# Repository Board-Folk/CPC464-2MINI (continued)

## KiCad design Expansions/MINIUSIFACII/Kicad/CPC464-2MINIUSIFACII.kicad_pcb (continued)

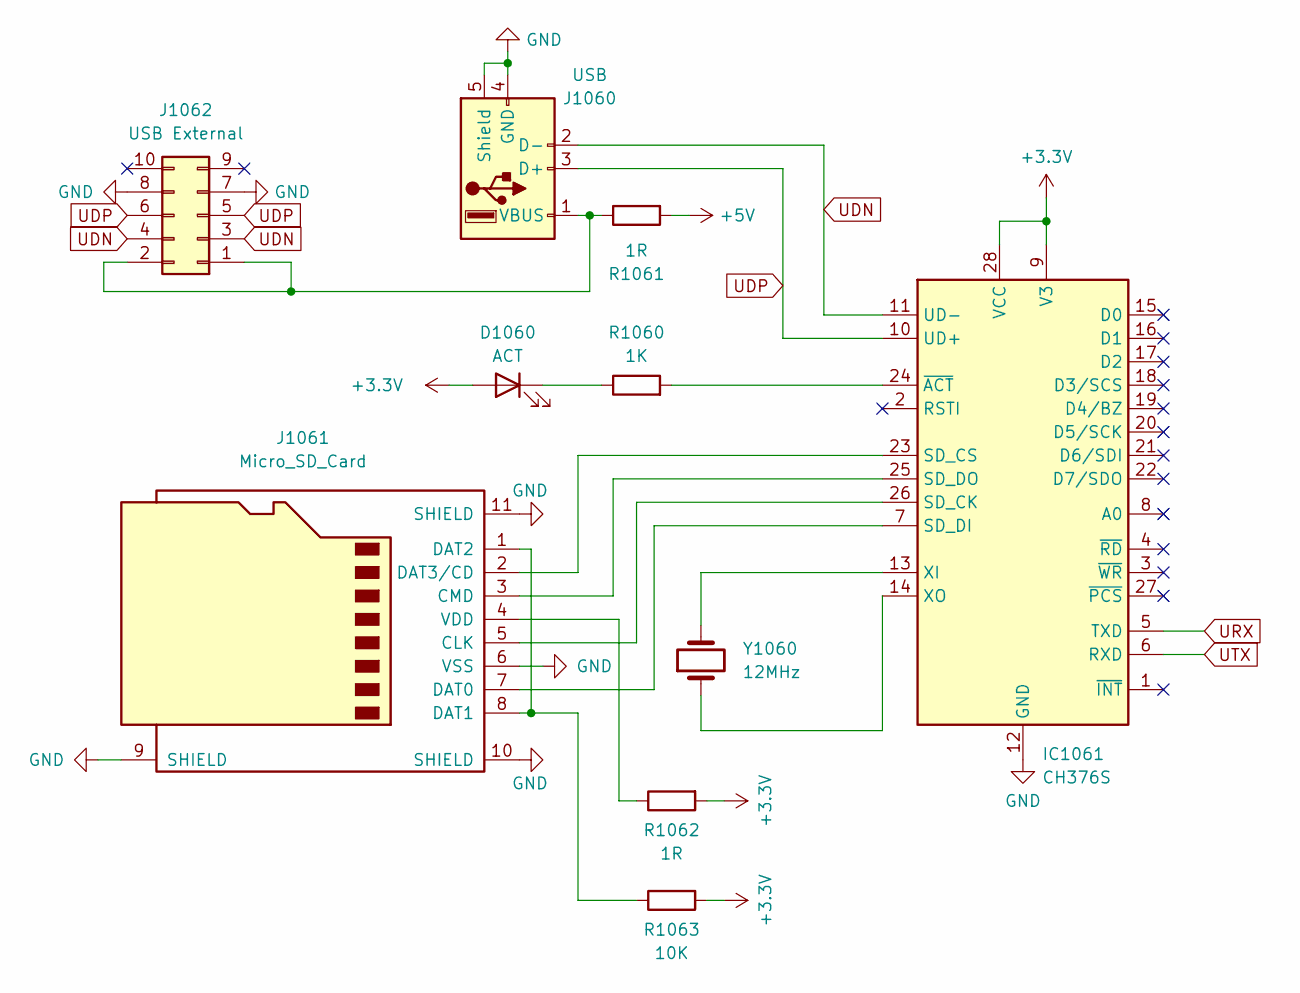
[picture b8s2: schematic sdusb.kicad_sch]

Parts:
D1060: ACT; LED_1206_3216Metric
IC1061: CH376S; SOIC-28W_7.5x17.9mm_P1.27mm
J1060: USB; USB_A_Molex_67643_Horizontal
J1061: Micro_SD_Card; microSD_HC_Hirose_DM3AT-SF-PEJM5
J1062: USB External; PinSocket_2x05_P2.54mm_Horizontal
R1060: 1K; R_0805_2012Metric
R1061, R1062: 1R; R_0805_2012Metric
R1063: 10K; R_0805_2012Metric
Y1060: 12MHz; Crystal_HC49-U_Vertical

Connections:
+3.3V: D1060.2 (A), IC1061.9 (V3), IC1061.28 (VCC), R1062.2, R1063.2; also elsewhere on the board
+5V: R1061.2; also elsewhere on the board
GND: IC1061.12 (GND), J1060.4 (GND), J1060.5 (Shield), J1061.6 (VSS), J1061.9 (SHIELD), J1061.10 (SHIELD), J1061.11 (SHIELD), J1062.7, J1062.8; also elsewhere on the board
unnamed: D1060.1 (K), R1060.1
unnamed: IC1061.7 (SD_DI), J1061.7 (DAT0)
unnamed: IC1061.13 (XI), Y1060.2
unnamed: IC1061.14 (XO), Y1060.1
unnamed: IC1061.23 (SD_CS), J1061.2 (DAT3/CD)
unnamed: IC1061.24 (~ACT), R1060.2
unnamed: IC1061.25 (SD_DO), J1061.3 (CMD)
unnamed: IC1061.26 (SD_CK), J1061.5 (CLK)
unnamed: J1060.1 (VBUS), J1062.1, J1062.2, R1061.1
unnamed: J1061.1 (DAT2), J1061.8 (DAT1), R1063.1
unnamed: J1061.4 (VDD), R1062.1
UDN: IC1061.11 (UD-), J1060.2 (D-), J1062.3, J1062.4
UDP: IC1061.10 (UD+), J1060.3 (D+), J1062.5, J1062.6
URX: IC1061.5 (TXD); also elsewhere on the board
UTX: IC1061.6 (RXD); also elsewhere on the board

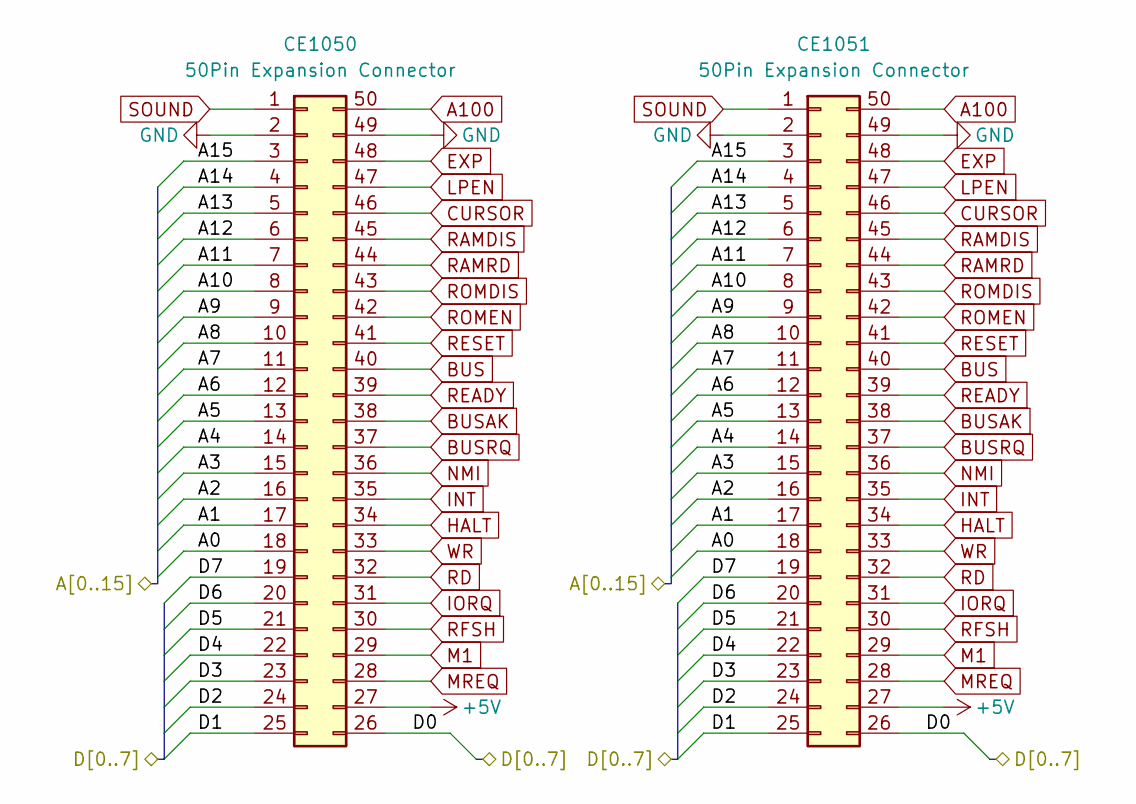
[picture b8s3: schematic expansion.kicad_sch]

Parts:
CE1050, CE1051: 50Pin Expansion Connector; EXPANSION_IDC_ANONYMISED

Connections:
+5V: CE1050.27, CE1051.27; also elsewhere on the board
/Expansion Ports/A0: CE1050.18, CE1051.18; also elsewhere on the board
/Expansion Ports/A1: CE1050.17, CE1051.17; also elsewhere on the board
/Expansion Ports/A2: CE1050.16, CE1051.16; also elsewhere on the board
/Expansion Ports/A3: CE1050.15, CE1051.15; also elsewhere on the board
/Expansion Ports/A4: CE1050.14, CE1051.14; also elsewhere on the board
/Expansion Ports/A5: CE1050.13, CE1051.13; also elsewhere on the board
/Expansion Ports/A6: CE1050.12, CE1051.12; also elsewhere on the board
/Expansion Ports/A7: CE1050.11, CE1051.11; also elsewhere on the board
/Expansion Ports/A8: CE1050.10, CE1051.10; also elsewhere on the board
/Expansion Ports/A9: CE1050.9, CE1051.9; also elsewhere on the board
/Expansion Ports/A10: CE1050.8, CE1051.8; also elsewhere on the board
/Expansion Ports/A11: CE1050.7, CE1051.7; also elsewhere on the board
/Expansion Ports/A12: CE1050.6, CE1051.6; also elsewhere on the board
/Expansion Ports/A13: CE1050.5, CE1051.5; also elsewhere on the board
/Expansion Ports/A14: CE1050.4, CE1051.4; also elsewhere on the board
/Expansion Ports/A15: CE1050.3, CE1051.3; also elsewhere on the board
/Expansion Ports/D0: CE1050.26, CE1051.26; also elsewhere on the board
/Expansion Ports/D1: CE1050.25, CE1051.25; also elsewhere on the board
/Expansion Ports/D2: CE1050.24, CE1051.24; also elsewhere on the board
/Expansion Ports/D3: CE1050.23, CE1051.23; also elsewhere on the board
/Expansion Ports/D4: CE1050.22, CE1051.22; also elsewhere on the board
/Expansion Ports/D5: CE1050.21, CE1051.21; also elsewhere on the board
/Expansion Ports/D6: CE1050.20, CE1051.20; also elsewhere on the board
/Expansion Ports/D7: CE1050.19, CE1051.19; also elsewhere on the board
A100: CE1050.50, CE1051.50
BUS: CE1050.40, CE1051.40; also elsewhere on the board
BUSAK: CE1050.38, CE1051.38
BUSRQ: CE1050.37, CE1051.37
CURSOR: CE1050.46, CE1051.46
EXP: CE1050.48, CE1051.48
GND: CE1050.2, CE1050.49, CE1051.2, CE1051.49; also elsewhere on the board
HALT: CE1050.34, CE1051.34
INT: CE1050.35, CE1051.35
IORQ: CE1050.31, CE1051.31; also elsewhere on the board
LPEN: CE1050.47, CE1051.47
M1: CE1050.29, CE1051.29; also elsewhere on the board
MREQ: CE1050.28, CE1051.28
NMI: CE1050.36, CE1051.36
RAMDIS: CE1050.45, CE1051.45
RAMRD: CE1050.44, CE1051.44
RD: CE1050.32, CE1051.32; also elsewhere on the board
READY: CE1050.39, CE1051.39; also elsewhere on the board
RESET: CE1050.41, CE1051.41
RFSH: CE1050.30, CE1051.30
ROMDIS: CE1050.43, CE1051.43; also elsewhere on the board
ROMEN: CE1050.42, CE1051.42; also elsewhere on the board
SOUND: CE1050.1, CE1051.1
WR: CE1050.33, CE1051.33

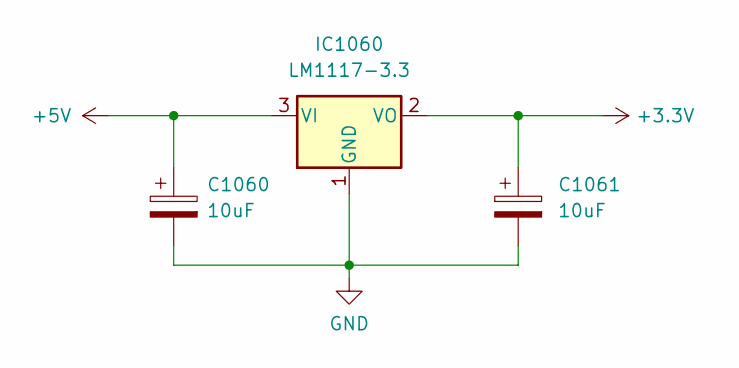
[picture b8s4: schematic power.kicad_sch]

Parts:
C1060, C1061: 10uF; CP_EIA-3216-18_Kemet-A
IC1060: LM1117-3.3; SOT-223-3_TabPin2

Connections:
+3.3V: C1061.1, IC1060.2 (VO); also elsewhere on the board
+5V: C1060.1, IC1060.3 (VI); also elsewhere on the board
GND: C1060.2, C1061.2, IC1060.1 (GND); also elsewhere on the board

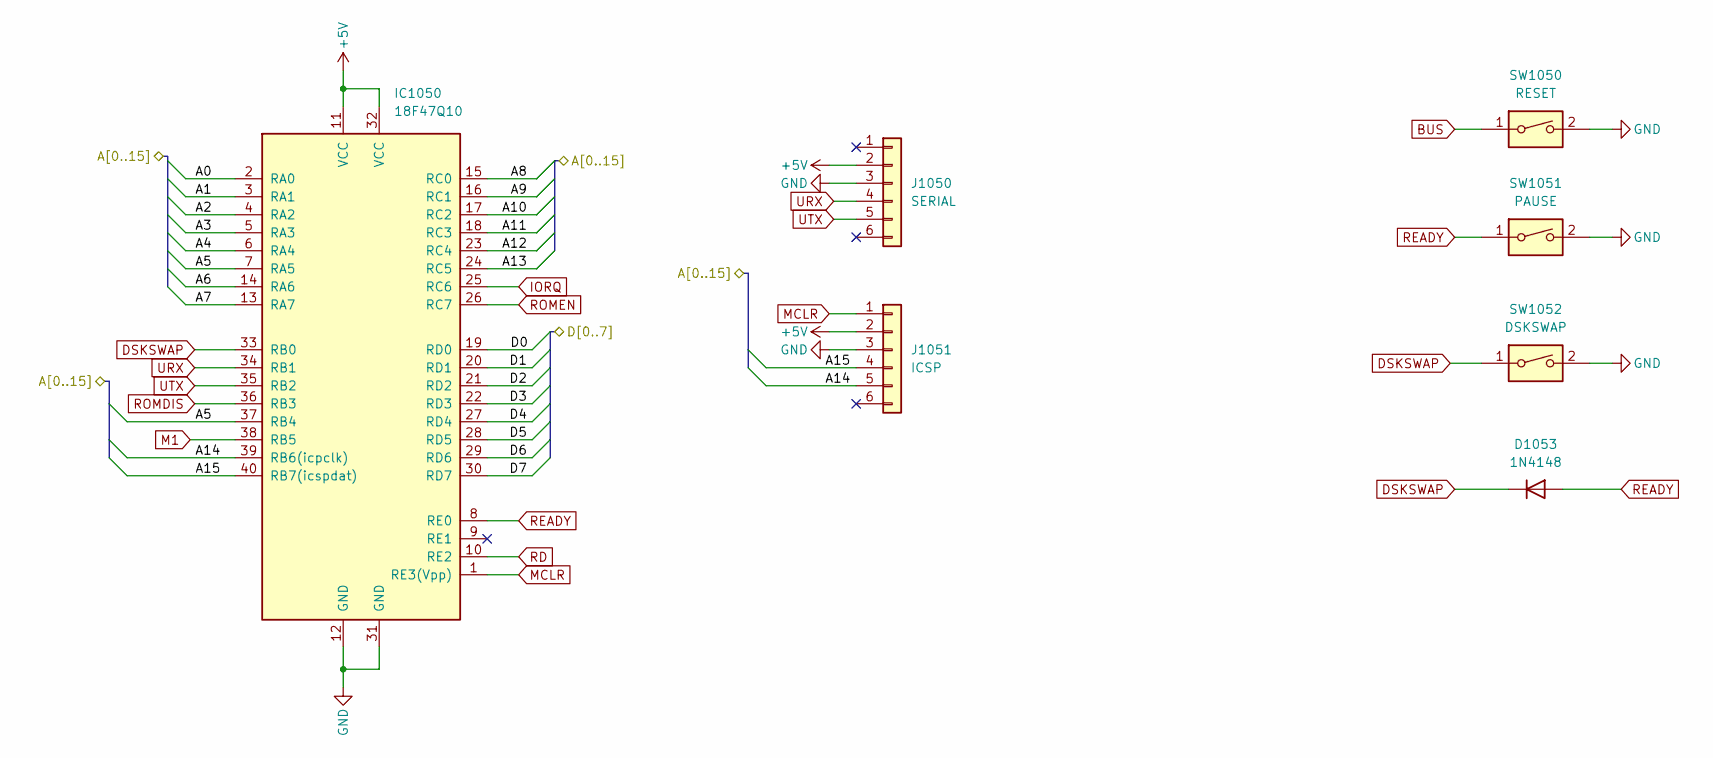
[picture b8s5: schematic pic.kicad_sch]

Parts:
D1053: 1N4148; D_SOD-123
IC1050: 18F47Q10; DIP-40_W15.24mm_Socket
J1050: SERIAL; PinSocket_1x06_P2.54mm_Horizontal
J1051: ICSP; PinHeader_1x06_P2.54mm_Horizontal
SW1050: RESET; SW_Tactile_SPST_Angled_PTS645Vx58-2LFS
SW1051: PAUSE; SW_Tactile_SPST_Angled_PTS645Vx58-2LFS
SW1052: DSKSWAP; SW_Tactile_SPST_Angled_PTS645Vx58-2LFS

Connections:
+5V: IC1050.11 (VCC), IC1050.32 (VCC), J1050.2, J1051.2; also elsewhere on the board
/Expansion Ports/A0: IC1050.2 (RA0); also elsewhere on the board
/Expansion Ports/A1: IC1050.3 (RA1); also elsewhere on the board
/Expansion Ports/A2: IC1050.4 (RA2); also elsewhere on the board
/Expansion Ports/A3: IC1050.5 (RA3); also elsewhere on the board
/Expansion Ports/A4: IC1050.6 (RA4); also elsewhere on the board
/Expansion Ports/A5: IC1050.7 (RA5), IC1050.37 (RB4); also elsewhere on the board
/Expansion Ports/A6: IC1050.14 (RA6); also elsewhere on the board
/Expansion Ports/A7: IC1050.13 (RA7); also elsewhere on the board
/Expansion Ports/A8: IC1050.15 (RC0); also elsewhere on the board
/Expansion Ports/A9: IC1050.16 (RC1); also elsewhere on the board
/Expansion Ports/A10: IC1050.17 (RC2); also elsewhere on the board
/Expansion Ports/A11: IC1050.18 (RC3); also elsewhere on the board
/Expansion Ports/A12: IC1050.23 (RC4); also elsewhere on the board
/Expansion Ports/A13: IC1050.24 (RC5); also elsewhere on the board
/Expansion Ports/A14: IC1050.39 (RB6(icpclk)), J1051.5; also elsewhere on the board
/Expansion Ports/A15: IC1050.40 (RB7(icspdat)), J1051.4; also elsewhere on the board
/Expansion Ports/D0: IC1050.19 (RD0); also elsewhere on the board
/Expansion Ports/D1: IC1050.20 (RD1); also elsewhere on the board
/Expansion Ports/D2: IC1050.21 (RD2); also elsewhere on the board
/Expansion Ports/D3: IC1050.22 (RD3); also elsewhere on the board
/Expansion Ports/D4: IC1050.27 (RD4); also elsewhere on the board
/Expansion Ports/D5: IC1050.28 (RD5); also elsewhere on the board
/Expansion Ports/D6: IC1050.29 (RD6); also elsewhere on the board
/Expansion Ports/D7: IC1050.30 (RD7); also elsewhere on the board
BUS: SW1050.1; also elsewhere on the board
DSKSWAP: D1053.1 (K), IC1050.33 (RB0), SW1052.1
GND: IC1050.12 (GND), IC1050.31 (GND), J1050.3, J1051.3, SW1050.2, SW1051.2, SW1052.2; also elsewhere on the board
IORQ: IC1050.25 (RC6); also elsewhere on the board
M1: IC1050.38 (RB5); also elsewhere on the board
MCLR: IC1050.1 (RE3(Vpp)), J1051.1
RD: IC1050.10 (RE2); also elsewhere on the board
READY: D1053.2 (A), IC1050.8 (RE0), SW1051.1; also elsewhere on the board
ROMDIS: IC1050.36 (RB3); also elsewhere on the board
ROMEN: IC1050.26 (RC7); also elsewhere on the board
URX: IC1050.34 (RB1), J1050.4; also elsewhere on the board
UTX: IC1050.35 (RB2), J1050.5; also elsewhere on the board

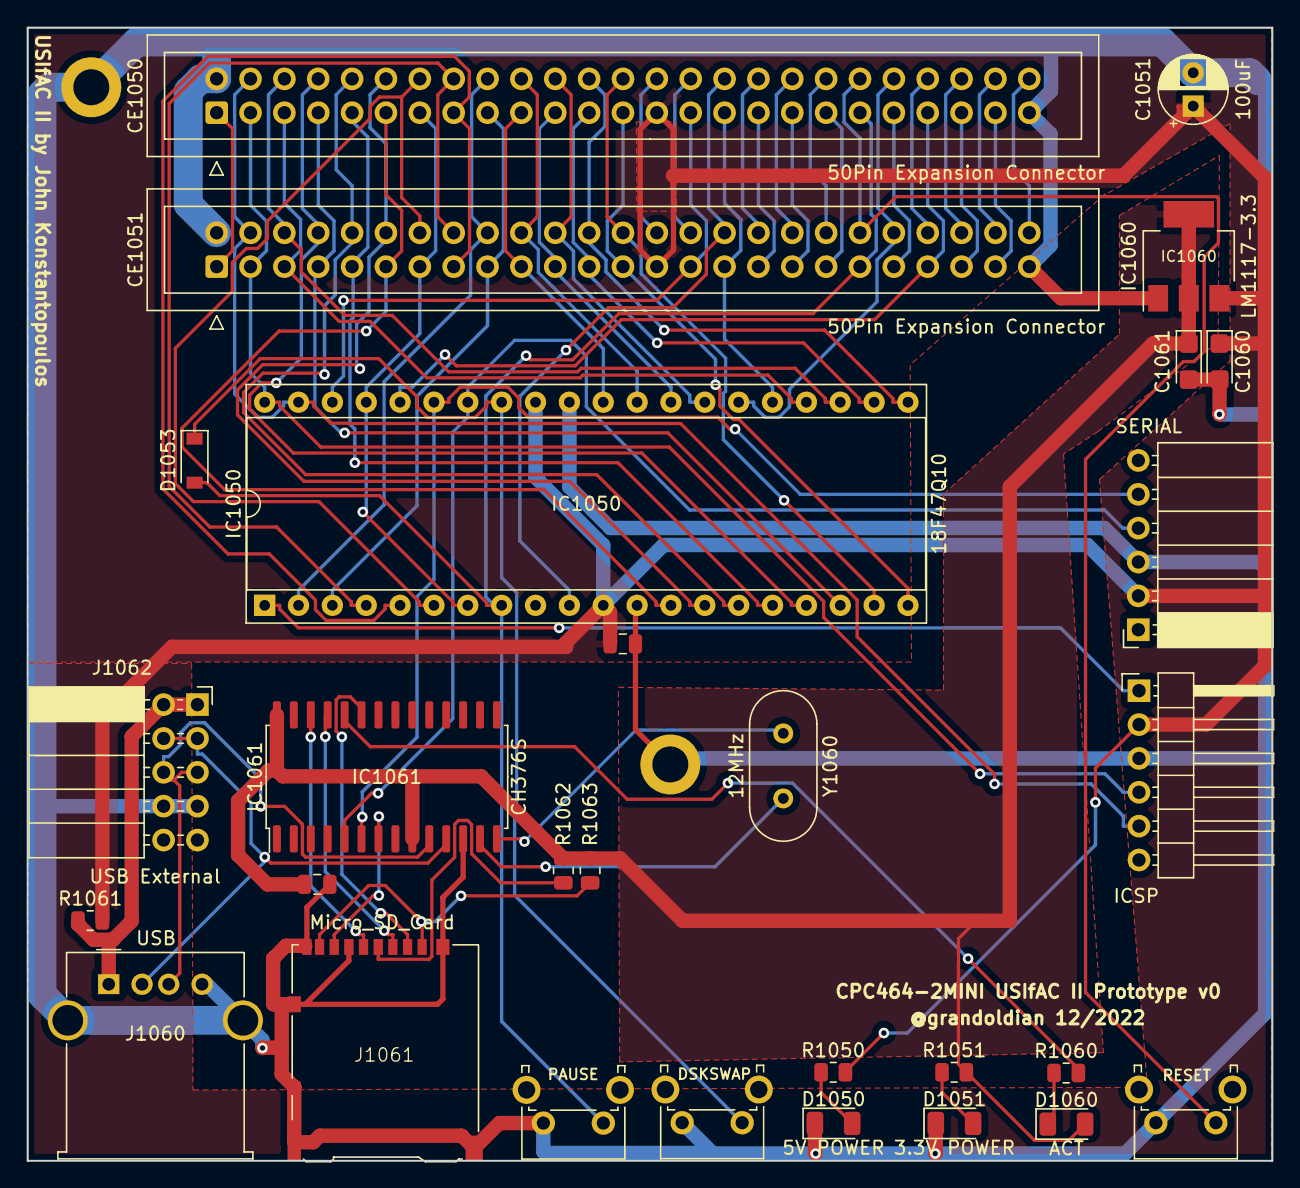
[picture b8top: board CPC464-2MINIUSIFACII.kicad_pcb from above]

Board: 2 copper layers, 93.4 x 85.0 mm, 31 parts (0 on the bottom side), 69 nets.

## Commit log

2023-11-04 Readmes
2023-11-05 Initial Push
2023-11-05 Readme Updates and 40007 Adapter
2023-11-05 Upload Photo
2024-02-13 Update Readme and Image
2024-02-13 Photos
2024-02-13 More Photos
2024-02-13 Readme Updates
